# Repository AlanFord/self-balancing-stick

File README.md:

# self-balancing-stick
# UPDATE:
With apologies, this project was clearly beyond my skill set.  However, I've made a lot of progress and am closing in on completion.  Many thanks to a couple of makerspaces - [HackRVA](https://www.hackrva.org/blog/) and [BuildRVA](https://buildrva.spaces.nexudus.com/en).

The Countdown:
* 10 - Study control system theory so as to verify that replacement motors (torques, speeds, etc.) can still work. A lot has changed in this area since I last studied it 45 years ago. (**Complete**)
* 9 - Determine new control parameters using said control system theory and MATLAB (love/hate relationship right there) (**Complete**)
* 8 - Learn Arduino programming (**Complete**)
* 7 - Learn to use machine tools such that I can fabricate parts ((**Complete**)
* 6 - Pause to build a claw machine (because who doesn't want a claw machine to pick up candy and plushies?) (**Complete**)
* 5 - Make the motor clamps from ABS on an X-Carve CNC router at HackRVA (**Complete**)
* 4 - Make the balancing point from acetal on a Sherline lathe at BuildRVA (**Complete**)
* 3 - Make the gyro mount from HDPE on a Grizzly manual lathe at BuildRVA (**Complete**)
* 2 - Make the motor mount block from aluminum on a Tormach 1100 CNC mill at BuildRVA (**Complete**)
* 1 - Fabricate the reaction wheels (**In Progress!**)
* Go! (In the Near Future)

Dual Axis Reaction Wheel Inverted Pendulum

This project is inspired by an earlier project by Mike Rouleau.  For details, read [Mike.md](../master/Mike.md).

My design looks similar to Mike's, but a lot of the components required substitutes
* Motors (unavailable) replaced with Pololu brushed DC motors and hubs
* Rotors modified to mount on the hubs
* Control system parameters modified to reflect new motor constants
* Motor drivers modified to match the motors
* Unique Arduino shield designed to support two motor drivers and a connector
for the gyro

My CAD work is being done in Fusion 360.  I haven't added those files to this repository yet, but in some cases drawings (in the form of PDFs) have been included.

Design of the control system is being done in Matlab and documented in LaTeX.  The
work can be found in the folders (you guessed it) matlab and latex.

The hardware is based on what I have at hand.  
* The shaft is a 1 ft length of 3003 Aluminum tube (McMaster Carr part number 7237K33)
* 4.4:1 Metal Gearmotor 25Dx48L mm MP 12V with 48 CPR Encoder (Pololu Part # 3237)
* Pololu Universal Aluminum Mounting Hub for 4mm Shaft, #4-40 Holes (2-Pack) (Pololu Part # 1081)
* Adafruit 9-DOF Absolute Orientation IMU Fusion Breakout - BNO055 (Adafruit Part # 2472)
* Gy-521 MPU-6050 Module 3 Axis Analog Gyro and Accelerometer (various suppliers on Amazon)

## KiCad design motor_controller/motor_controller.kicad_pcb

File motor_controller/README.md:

# Arduino Shield for the Self-Balancing Stick

The design for the Arduino shield is intended to include motor drivers for two dc motors as well as the interface for a GY-521 Gyro.

The motor drivers each use a MAX14780 motor driver IC. A barrel jack (2.1 mm, center-positive) on the shield provides power for the motors (12V, 4.2A max).  Separate pin headers are made available for connecting the motors and the GY-521 gyro.  The motors are Pololu 4.4:1 gear motors witha 48 CPR encoder, requireing a 6-pin connector.  The GY-521 interface also requires a 6-pin connector.

The Arduino pins used by each of the connectors are as follows:

GY-521 -> Arduino
* SCL -> A5/SCL
* SDA -> A4/SDA
* INT -> A3

Left Motor -> Arduino
* Vcc -> +5V
* PWM -> D7
* DIR -> D8
* Encoder_A -> D2 (Interrrupt 0)
* Encoder_B -> A2

Right Motor -> Arduino
* Vcc -> +5V
* PWM -> D12
* DIR -> D13
* Encoder_A -> D3 (Interrupt 1)
* Encoder_B -> D6

The shield contains LEDs for both motors that indicate the direction the motor is being driven.
* Red LED -> DIR=1 (Clockwise)
* Green LED -> DIR=0 (Counterclockwise)

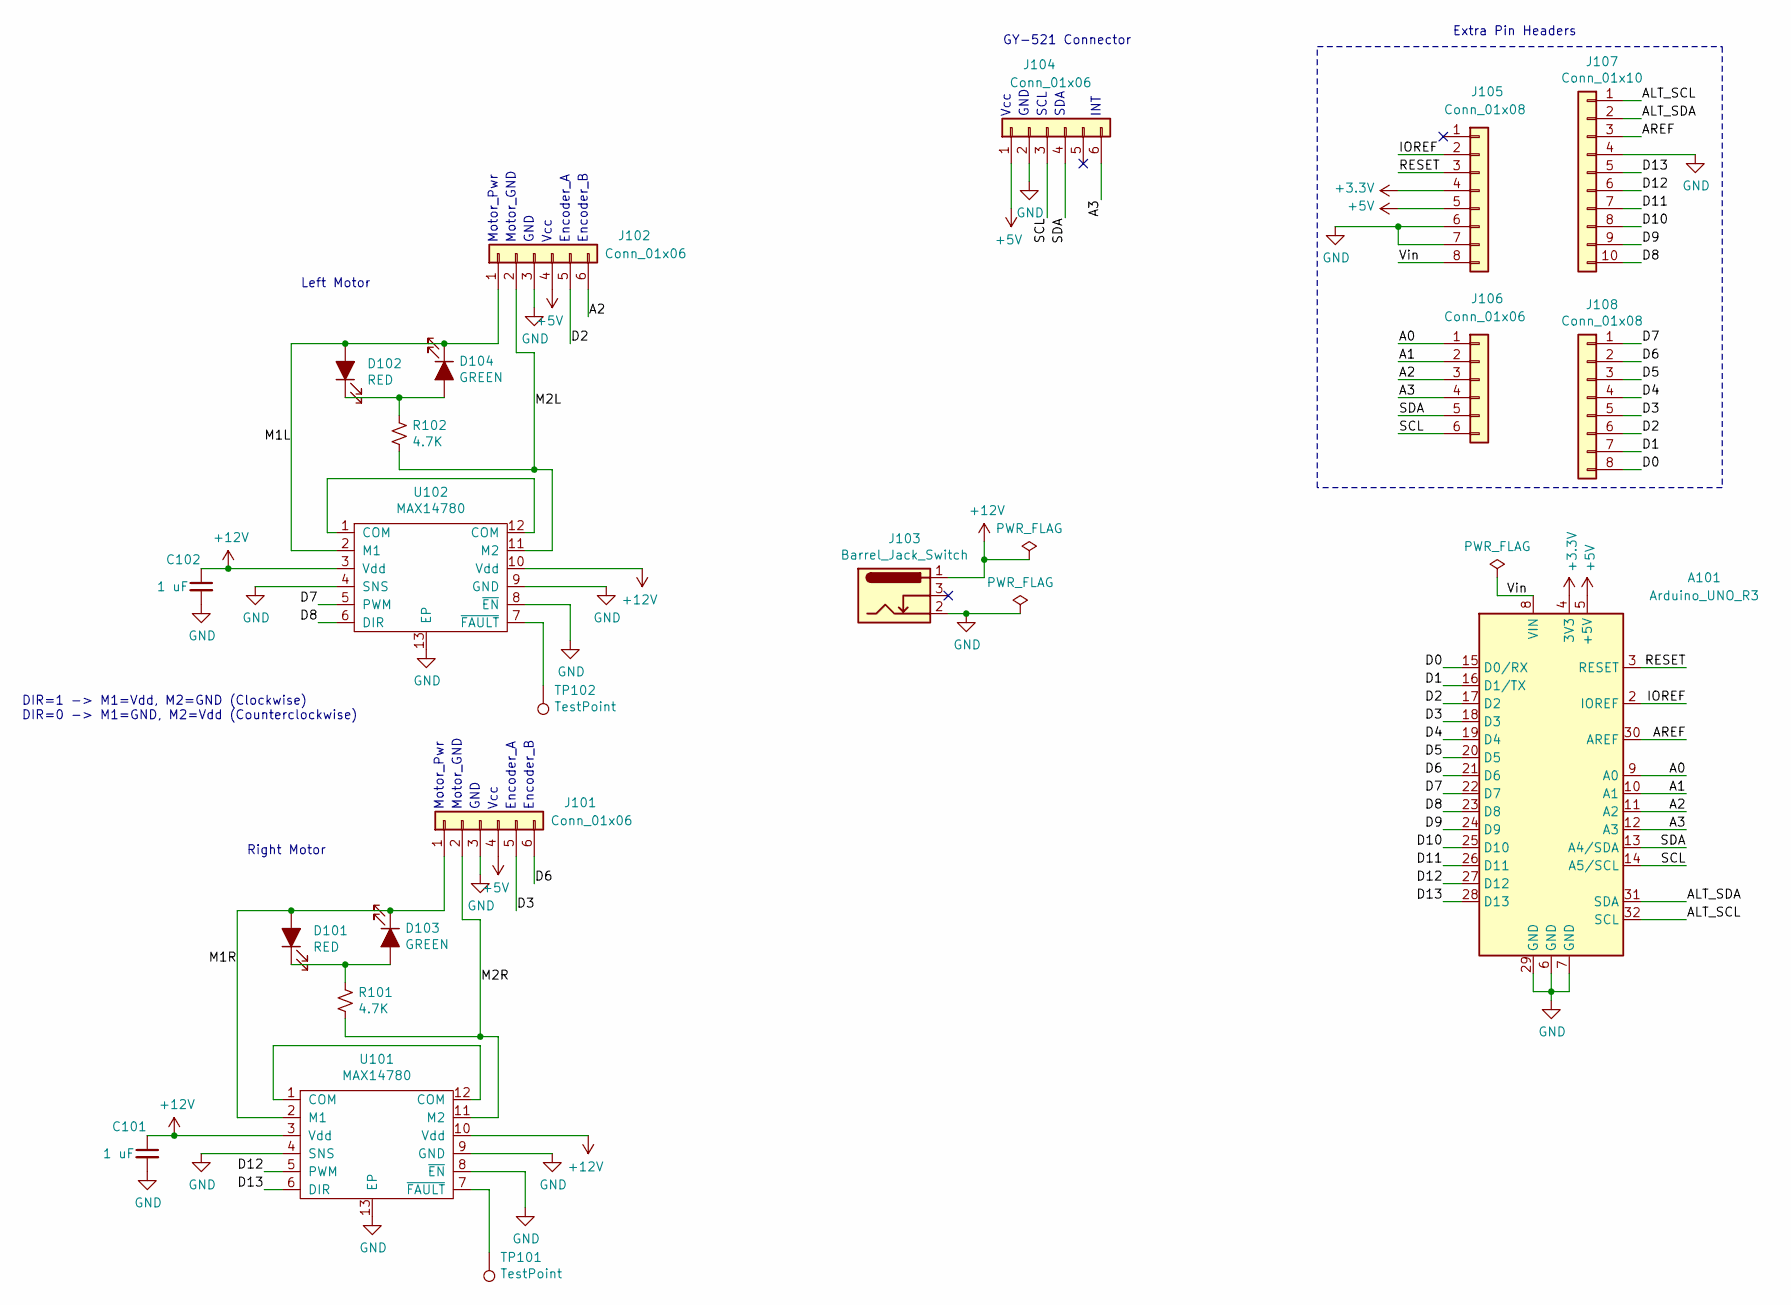
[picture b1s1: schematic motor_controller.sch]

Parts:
A101: Arduino_UNO_R3
C101, C102: 1 uF; C_0805_2012Metric
D101, D102: RED; LED_0805_2012Metric
D103, D104: GREEN; LED_0805_2012Metric
J101, J102, J104, J106: Conn_01x06; PinHeader_1x06_P2.54mm_Vertical
J103: Barrel_Jack_Switch; BarrelJack_CUI_PJ-102AH_Horizontal
J105, J108: Conn_01x08; PinHeader_1x08_P2.54mm_Vertical
J107: Conn_01x10; PinHeader_1x10_P2.54mm_Vertical
R101, R102: 4.7K; R_0805_2012Metric
TP101, TP102: TestPoint; TestPoint_Pad_D2.0mm
U101, U102: MAX14780; max14870

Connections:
+3V3: A101.4 (3V3), J105.4
+5V: A101.5 (+5V), J101.4, J102.4, J104.1, J105.5
+12V: C101.1, C102.1, J103.1, U101.3 (Vdd), U101.10 (Vdd), U102.3 (Vdd), U102.10 (Vdd); also elsewhere on the board
/A0: A101.9 (A0), J106.1
/A1: A101.10 (A1), J106.2
/A2: A101.11 (A2), J102.6, J106.3
/A3: A101.12 (A3), J104.6, J106.4
/ALT_SCL: A101.32 (SCL), J107.1
/ALT_SDA: A101.31 (SDA), J107.2
/AREF: A101.30 (AREF), J107.3
/D0: A101.15 (D0/RX), J108.8
/D1: A101.16 (D1/TX), J108.7
/D2: A101.17 (D2), J102.5, J108.6
/D3: A101.18 (D3), J101.5, J108.5
/D4: A101.19 (D4), J108.4
/D5: A101.20 (D5), J108.3
/D6: A101.21 (D6), J101.6, J108.2
/D7: A101.22 (D7), J108.1, U102.5 (PWM)
/D8: A101.23 (D8), J107.10, U102.6 (DIR)
/D9: A101.24 (D9), J107.9
/D10: A101.25 (D10), J107.8
/D11: A101.26 (D11), J107.7
/D12: A101.27 (D12), J107.6, U101.5 (PWM)
/D13: A101.28 (D13), J107.5, U101.6 (DIR)
/IOREF: A101.2 (IOREF), J105.2
/M1L: D102.2 (A), D104.1 (K), J102.1, U102.2 (M1)
/M1R: D101.2 (A), D103.1 (K), J101.1, U101.2 (M1)
/M2L: J102.2, R102.2, U102.11 (M2)
/M2R: J101.2, R101.2, U101.11 (M2)
/RESET: A101.3 (RESET), J105.3
/SCL: A101.14 (A5/SCL), J104.3, J106.6
/SDA: A101.13 (A4/SDA), J104.4, J106.5
/Vin: A101.8 (VIN), J105.8
GND: A101.6 (GND), A101.7 (GND), A101.29 (GND), C101.2, C102.2, J101.3, J102.3, J103.2, J104.2, J105.6, J105.7, J107.4, U101.4 (SNS), U101.8 (~EN), U101.9 (GND), U101.13 (EP), U102.4 (SNS), U102.8 (~EN), U102.9 (GND), U102.13 (EP); also elsewhere on the board
unnamed: D101.1 (K), D103.2 (A), R101.1
unnamed: D102.1 (K), D104.2 (A), R102.1
unnamed: TP101.1, U101.7 (~FAULT)
unnamed: TP102.1, U102.7 (~FAULT)
unnamed: U101.1 (COM), U101.12 (COM)
unnamed: U102.1 (COM), U102.12 (COM)

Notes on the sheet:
Right Motor
Vcc
GND
SCL
SDA
INT
GY-521 Connector
Motor_Pwr
Motor_GND
Encoder_A
Encoder_B
Extra Pin Headers
Left Motor
DIR=1 -> M1=Vdd, M2=GND (Clockwise) DIR=0 -> M1=GND, M2=Vdd (Counterclockwise)

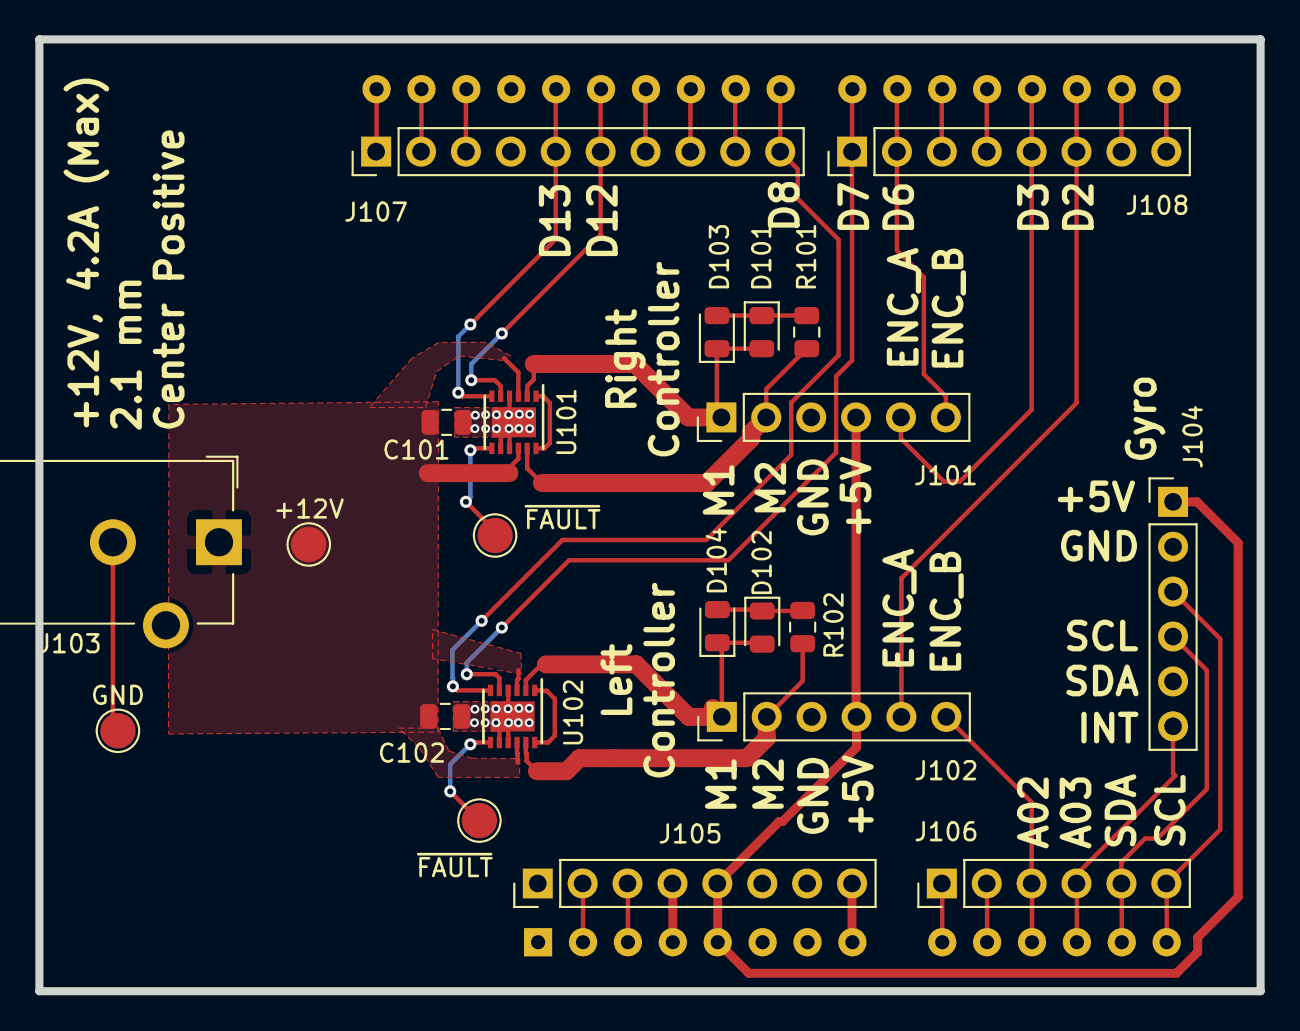
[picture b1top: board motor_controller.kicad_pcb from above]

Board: 2 copper layers, 69.1 x 53.8 mm, 21 parts (1 on the bottom side), 38 nets.

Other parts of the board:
+12V: TestPoint_Pad_D2.0mm
GND: TestPoint_Pad_D2.0mm

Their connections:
+12V: +12V.1; also elsewhere on the board
GND: GND.1; also elsewhere on the board

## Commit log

2017-08-20 included Mike Rouleau's design for reference
2017-08-20 added notes and converted pptx to pdf
2017-10-16 added 3d print files, references, modified reaction wheel to match pololu hubs and motors
2017-10-29 added nucleo references
2017-11-02 added references for BNO055
2019-04-01 updated readme to begin documenting current design
2019-04-01 added gitignore for the nucleo cube tree
2019-04-01 deleting the cube directory from the latest commit
2019-04-02 big catch-up commit
2019-04-03 cleaning up file structure
2019-04-03 cleaning up the latex files
2019-04-04 first cut at Arduino software
2019-04-05 rearrange harware files and add drawing of simple reaction wheel
2019-04-07 updated drawing of simplified reaction wheel
2019-04-17 drawings of major parts to be fabricated
2019-04-29 updated motor mount clip drawing
2019-04-30 added fabrication notes for the motor mounting clip
2019-05-01 added svg of motor mount clip used for x-carve
2019-05-31 cleaned up the latex document
2019-05-31 removing temporary latex files
2019-11-20 wiring schematic added and arduino software updated with pin definitions to match
2020-01-18 update Arduino software to use a motor driver based on the MAX14870 IC
2020-01-18 add KICAD design for the motor controller and gyro shield
2020-01-20 corrected pin definitions for the Pololu Dual MAX14870 motor driver shield
2020-01-20 updated schematic pdf and generated gerber files
2020-01-26 cleaned up main folder and added gy-521 test program
2020-01-27 documenting the code files
2020-01-27 added some documentation and updated some values to match the Pololu motors
2020-01-28 cleaned up test code in the main loop
2020-01-30 added and updated testing functions
2020-01-30 updated IMU offsets to reflect measured values from the calibrateIMU sketch
2020-01-30 corrected the encoder_PPR constant from 12 to 52.8 to reflect the 4.4:1 gear ratio
2020-01-30 rearranged folders, removed cruft, and updated README files
2020-01-31 updated gitignore
2020-01-31 improved dimension callouts for gyro mounting block drawing
2020-01-31 initial machining plan
2020-01-31 added pdf of machining plan
2020-02-01 beginning of atooling checklist
2020-02-01 more testing sketches
2020-02-02 tweeked the header comments for the simulation file
2020-02-02 finished tool list
2020-02-07 fully functioning encoder test sketch #2
2020-02-07 add drawing of pendulum tip
2021-10-02 updating to reflect as-built design
2021-10-02 updating the structure of the folders
2021-10-02 update schematic for newer version of Kicad
2021-10-08 first cut at STM#@ firmware
2021-10-08 complete population of mcu folder
2021-10-08 clean up file and directory names
2021-10-08 First clean compile
2021-10-10 create an stm32f746 version with more ram
2021-10-12 Update to usart3 for the F746. Also, begin to comment the code.
2021-10-12 more comments
2021-10-14 correct the LED port and pin
2021-10-14 remove f030 version for now
2021-10-14 convert SerialInterface structure to a class
2021-10-14 Add a readme for the STM32 firmware
2021-10-14 convert function to private method and cleanup comments
2021-10-14 create LED class and an enum for return codes
2021-10-15 convert Tick to a class
2021-10-15 Implement new terminal parser and clean up include files
2021-10-15 more cleanup
2021-10-15 more cleanup
    more
2021-10-16 add terminal commands and fix printf usage
2021-10-19 ensure Nodate's printf routine is used rather than stdlib
2021-10-23 Initial cut at mpu6050 interface
2021-10-24 Adding nodate commands
2021-10-31 imu, mpu6050 and I2Cdev compile
2021-11-02 initial motor and encoder classes
2021-11-17 fleshed out files and corrected compilation bugs
2021-12-03 first commit of STM32 HAL version of firmware (work in progress)
2021-12-04 Add interrupt service for Timer1 and and a Timer1 filter
2021-12-05 shuffle timers, add a microsec clock, and flesh out the encoder
2021-12-08 converting project to C++ to support using the IMU code
2021-12-08 more i2cdev and mpu6050 changes to accommodate STM32 HAL
2021-12-09 more changes for successful compilation
2021-12-09 added "extern C" wrappers
2021-12-09 converted motor functions to a Motor class
2021-12-09 added encoder and imu status returns
2021-12-09 remove unneeded include file
    remove unneeded include file
2021-12-09 Added a Controller class
2021-12-10 complete version of the Controller class
2021-12-11 add hardware interface design notes
2021-12-11 limit motor pwm to <50kHz
2021-12-11 Make the controller functional
2021-12-11 correct the encoder counts per rev
2021-12-11 set the I2c rise and fall times to non-zero values
2021-12-12 two bug fixes
2021-12-14 Changed I2C1 SCL from PB6 to PB8
2021-12-16 correct I2Cdev HAL interface and up the uart speed
2021-12-17 swap pins to be consistent with Arduino Uno for imu interrupt
2021-12-18 annotate the imu class
2021-12-25 utility to calculate stm32 I2C timing register value
2021-12-29 functional polling version with initial reset
2021-12-29 remove debug statements from I2Cdev.c
2021-12-30 working set of accel and gyro offsets
2021-12-30 renamed register project to timing so as to better reflect purpose
2022-01-04 functional test of c++ mpu6050 library raw data calls
2022-01-07 fix big/little endian issues and add return code testing
2022-01-09 functioning basic gyro and accelerometer testing
2022-01-19 functioning dmp test routine (polling)
2022-01-19 update odds and ends
2022-01-19 update STM32CUBEIDE to 1.8.0, changing generated files
2022-01-21 functional interrupt-driven dmp test
2022-01-21 initial (not successful) attempt to use v6.12 MotionApps firmware
2022-01-23 refactor for clarity and add more comments
2022-01-24 cleanup, initialize variables, and add comments
2022-01-25 more comments and cleaning up constants
    cleanup
2022-01-27 Add more comments
2022-01-28 somethings broken
2022-01-29 add imu to the command list
2022-01-29 broken, but working on it
2022-01-29 changed global objects to global pointers
2022-02-03 integrate new dmp FIFO handling routine
2022-02-04 added "table of symbols" to the documentation and updated .gitignore
2022-02-06 Editorial fixes and corrected equations in the documentation
2022-02-09 Initial attempt at an Implementation section in docs
2022-02-12 clean up the introduction of rotor velocity feedback
2022-02-12 add a matlab flag to determine regular or simple rotor parameters
2022-02-19 fixed gear ratio discussion, shaft work, and implementation details
2022-02-20 improved method for determining motor constants
2022-02-24 updated measured motor data
2022-02-24 change TODO to FIXME, improving task sorting in IDE
2022-03-02 something's wrong
2022-03-02 add digital filter class
2022-03-02 modify imu class to use filter class
2022-03-02 add fixme comments
2022-03-03 corrected needed externs
2022-03-03 change strtol to strtof when processing commands
2022-03-03 sort out true, false, error definition conflicts
2022-03-03 add extended data edit to terminal feature
2022-03-03 refactored use of theta/omega in imu methods
2022-03-03 finish extended data edit
2022-03-04 create OFF, MANUAL, AUTO controller modes
2022-03-05 implement remaining command line features
2022-03-07 update source commenting
2022-03-09 move calculation of the integral of angle error to the controller
2022-03-10 move angle_Zero calculation to controller class
    Moved the calculation of the reference (or zero) angle from the imu class to the controller class.
2022-03-11 clear some initializer compiler warnings and harden the enums
2022-03-11 use MPU6050 library version of GetCurrentFIFOPacket
2022-03-12 correct the TIMER 5 prescaler to reflect a 1 usec counter
2022-03-13 cleanup matlab files
2022-03-13 update description of motor constant measurement
2022-03-15 Update transfer function coefficients
2022-04-19 correct docs and start state space model
2022-04-19 start of state space
2022-04-20 clean up the basic state space description
2022-04-25 more state space development
2022-05-02 state space updates
2022-07-21 clean up some comments
2022-07-24 Added acrylic reaction wheel design
2023-03-12 fix typos
2023-04-08 reorganizing references
2023-04-08 moving away from the nodate option
2023-06-03 add a text description
2023-06-04 beginnings of a client
2023-06-05 test of qt designer
2023-06-06 client with working tabs
2023-06-06 add button to control changing target voltages
